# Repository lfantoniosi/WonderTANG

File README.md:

# WonderTANG

# NOTE: New firmware for 2.02b boards at:

https://github.com/lfantoniosi/new-juice

## TangNano 20K cartridge for MSX computers

This cartridge allows any MSX computer to host a Sipeed Tang Nano 20K. The current fpga core implements:

- MicroSD Nextor 2.1 Drive
- FM OPLL + MSX Music ROM
- 2MB Super Mega RAM SCC+
- 4MB Memory Mapper
- Sega Master System VDP + PSG to allow running SMS roms from SofaRun (Franky HDMI)

## The Super Mega RAM SCC+

The Super Mega RAM SCC+ is a different ACVS-like MegaRam that support different mappers:

- Konami4 (2MB)
- Konami5 SCC+ (512KB)
- ASCII8 (2MB)
- ASCII16 (2MB)

Use the utility SMRAM.COM to allow using different mappers as well activating the SCC+, otherwise it will just work like an ordinary MegaRAM 2MB.

## Board Revisions

The latest available version is [V2.0b](#v20av20b-new). Please, use that version to order new boards.

> [!IMPORTANT]
> Always check your board revision when assembling or programming your WonderTANG.
>
> The revision number is available on the front-left side of the board.
>
> Download the specific [FPGA Bitstream version](#fpga-bitstream-versions) required by your board version.

### [V2.0a/V2.0b (NEW)](https://github.com/lfantoniosi/WonderTANG/tree/4a21359a5136a5a96363da55edc5d934acfd37c5/kicad/)

This is the new version using Tang Nano 20K internal DAC amplifier.

Changes since last revision:
* uses internal DAC for audio output
* switches to a flatter audio connector
* removes jumpers
* requires the latest [FPGA bitstream version](#fpga-bitstream-versions)

V2.0a is equivalent to V2.0b.

||
|:--|
|V2.0a prototype build|

|||
|-|-|
|V2.0b front render|V2.0b back render|

#### PCB

You can access V2.0b gerber files from github at:

[https://github.com/lfantoniosi/WonderTANG/tree/4a21359a5136a5a96363da55edc5d934acfd37c5/kicad/gerber](https://github.com/lfantoniosi/WonderTANG/tree/4a21359a5136a5a96363da55edc5d934acfd37c5/kicad/gerber)

I recommend JLCPCB: https://jlcpcb.com/

#### Bill of Materials

| Reference                   | Value                      | Description                                          | Qty | Link        |
|-----------------------------|----------------------------|------------------------------------------------------|-----|-------------|
| C5, C6, C7, C8, C9, C10, C11, C12 | DIP-100NF                  | MLCC Monolithic Ceramic Capacitor DIP 100nF (104)     | 8   | AliExpress  |
| C1, C2                      | ELEC-DIP-4.7UF-16V         | Electrolytic Capacitor DIP 4.7uF 16V                 | 2   | AliExpress  |
| C13                         | ELEC-DIP-10UF-16V          | Electrolytic Capacitor DIP 10uF 16V                  | 1   | AliExpress  |
| R5,R6                       | DIP-2.2K                   | Resistor PTH 2.2KR                                   | 2   | Aliexpress  |
| R1                          | DIP-330R                   | Resistor PTH 330R                                    | 1   | AliExpress  |
| R4                          | DIP-4.7K                   | Resistor PTH 4.7KR                                   | 1   | AliExpress  |
| D1                          | LED-3MM                    | LED 3MM Red                                          | 1   | AliExpress  |
| D2                          | 1N5817                     | SCHOTTKY BARRIER RECTIFIER DIODE                    | 1   | AliExpress  |
| U1, U2, U3, U4, U6          | SOCKET-DIP-NARROW-20       | DIP Socket Narrow 20 pins                            | 5   | AliExpress  |
| U1, U2, U3, U4, U6          | SN74LVC245AN               | OCTAL BUS TRANSCEIVER WITH 3-STATE OUTPUTS           | 5   | See note    |
| Q1,Q2                       | 2N3904                     | 2N3904 NPN switching Transistor                      | 2   | AliExpress  |
| J2                          | CP1-3523N                  | CONN JACK STEREO 3.5MM R/A                           | 1   | AliExpress  |
| J3                          | Mini Micro male/female JST | Mini Micro male/female JST                           | 1   | AliExpress  |
| U5                          | Tang Nano 20K              | Tang Nano 20K                                        | 1   | AliExpress  |

#### Build Notes

The audio J3 needs to be soldered into the TANG Nano 20K speaker pins (two small pins between the words SiPEED and TANG NANO 20K, polarity does not matter). Use the JST connector or solder it directly under the board.

#### 74LVC245AN

Be aware of fake 74VLC245 sold from Chinese vendors like AliExpress or UTSource. There are reports of they being 74LS245 rebranded as LVC which does not work. You need genuine 75LVC245. Buy then from DigiKey, Mouser or Adafruit.

### [V1.02d (PREVIOUS)](https://github.com/lfantoniosi/WonderTANG/tree/0e938fb70acad34c753a95fd54bb3fdd6095d590/kicad/)

> [!WARNING]
> If you are building new boards, please use the latest available board revision instead.

This version fixes a problem with Philips MSX machines (detected on [Philips VG8235](https://www.msx.org/wiki/Philips_VG-8235) and [Philips NMS8245](https://www.msx.org/wiki/Philips_NMS_8245)) by properly implementing the MSX cartridge nINT signal as an open-collector.

Changes since last revision:
* uses a transistor to implement nINT as open-collector
* requires a specific [FPGA bitstream version](#fpga-bitstream-versions)

|||
|-|-|
|V1.02d front render|V1.02d back render|

#### PCB

You can access V1.02d gerber files from github at:

[https://github.com/lfantoniosi/WonderTANG/tree/0e938fb70acad34c753a95fd54bb3fdd6095d590/kicad/gerber](https://github.com/lfantoniosi/WonderTANG/tree/0e938fb70acad34c753a95fd54bb3fdd6095d590/kicad/gerber)

#### Bill of Materials

| Reference                   | Value                      | Description                                          | Qty | Link        |
|-----------------------------|----------------------------|------------------------------------------------------|-----|-------------|
| C5, C6, C7, C8, C9, C10, C11, C12 | DIP-100NF                  | MLCC Monolithic Ceramic Capacitor DIP 100nF (104)     | 8   | AliExpress  |
| C1, C3, C13                 | ELEC-DIP-10UF-16V          | Electrolytic Capacitor DIP 10uF 16V                  | 3   | AliExpress  |
| C2, C4                      | DIP-1UF                    | MLCC Monolithic Ceramic Capacitor DIP 1uF (105)      | 2   | AliExpress  |
| R2, R3                      | DIP-47R                    | Resistor PTH 47R                                     | 2   | AliExpress  |
| R5,R6                       | DIP-2.2K                   | Resistor PTH 2.2KR                                   | 2   | Aliexpress  |
| R1                          | DIP-330R                   | Resistor PTH 330R                                    | 1   | AliExpress  |
| R4                          | DIP-4.7K                   | Resistor PTH 4.7KR                                   | 1   | AliExpress  |
| D1                          | LED-3MM                    | LED 3MM Red                                          | 1   | AliExpress  |
| D2                          | 1N5817                     | SCHOTTKY BARRIER RECTIFIER DIODE                    | 1   | AliExpress  |
| U1, U2, U3, U4, U6          | SOCKET-DIP-NARROW-20       | DIP Socket Narrow 20 pins                            | 5   | AliExpress  |
| U1, U2, U3, U4, U6          | SN74LVC245AN               | OCTAL BUS TRANSCEIVER WITH 3-STATE OUTPUTS           | 5   | See note above  |
| Q1,Q2                       | 2N3904                     | 2N3904 NPN switching Transistor                      | 2   | AliExpress  |
| C13                         | ELEC-DIP-10UF-16V          | Electrolytic Capacitor DIP 10uF 16V                  | 1   | AliExpress  |
| C1, C2                      | ELEC-DIP-4.7UF-16V         | Electrolytic Capacitor DIP 7.7uF 16V                 | 2   | AliExpress  |
| J1, J3                      | PH-254-S-M-40-BLACK        | 2.54mm 1 x 40 Pin Male Single Row Pin Header Strip Black | 1 | AliExpress  |
| J2                          | SJ1-3533NG                 | SJ1-3533NG Audio P4 3 Pin connector                  | 1   | AliExpress  |
| U5                          | Tang Nano 20K              | Tang Nano 20K                                        | 1   | AliExpress  |

### [V1.01c (OBSOLETE)](https://github.com/lfantoniosi/WonderTANG/tree/b9e608418bb1917098046716af13b877def6737b/kicad/)

> [!WARNING]
> If you are building new boards, please use the latest available board revision instead.

This version corrects an audio problem due to wrong connection of AUDIO and SOUNDIN capacitors.

Changes since last revision:
* fix audio output
* requires an old [FPGA bitstream version](#fpga-bitstream-versions)

> [!IMPORTANT]
> This version is known to experience problems with some Philips MSX machines.

|||
|-|-|
|V1.01c front render|V1.01c back render|

#### PCB

You can access V1.01c gerber files from github at:

[https://github.com/lfantoniosi/WonderTANG/tree/b9e608418bb1917098046716af13b877def6737b/kicad/gerber](https://github.com/lfantoniosi/WonderTANG/tree/b9e608418bb1917098046716af13b877def6737b/kicad/gerber)

Or you can order V1.01c PCBs directly from:

[https://www.pcbway.com/project/shareproject/WonderTANG_v1_01c_ba2c16ea.html](https://www.pcbway.com/project/shareproject/WonderTANG_v1_01c_ba2c16ea.html)

A small part of the money will be donated to the author of the project.

#### Bill of Materials

| Reference                   | Value                      | Description                                          | Qty | Link        |
|-----------------------------|----------------------------|------------------------------------------------------|-----|-------------|
| C5, C6, C7, C8, C9, C10, C11, C12 | DIP-100NF                  | MLCC Monolithic Ceramic Capacitor DIP 100nF (104)     | 8   | AliExpress  |
| C1, C3, C13                 | ELEC-DIP-10UF-16V          | Electrolytic Capacitor DIP 10uF 16V                  | 3   | AliExpress  |
| C2, C4                      | DIP-1UF                    | MLCC Monolithic Ceramic Capacitor DIP 1uF (105)      | 2   | AliExpress  |
| R2, R3                      | DIP-47R                    | Resistor PTH 47R                                     | 2   | AliExpress  |
| R1                          | DIP-330R                   | Resistor PTH 330R                                    | 1   | AliExpress  |
| R4                          | DIP-4.7K                   | Resistor PTH 4.7KR                                   | 1   | AliExpress  |
| R5                          | DIP-2.2K                   | Resistor PTH 2.2KR                                   | 1   |             |
| D1                          | LED-3MM                    | LED 3MM Red                                          | 1   | AliExpress  |
| D2                          | 1N5817                     | SCHOTTKY BARRIER RECTIFIER DIODE                    | 1   | AliExpress  |
| U1, U2, U3, U4, U6          | SOCKET-DIP-NARROW-20       | DIP Socket Narrow 20 pins                            | 5   | AliExpress  |
| U1, U2, U3, U4, U6          | SN74LVC245AN               | OCTAL BUS TRANSCEIVER WITH 3-STATE OUTPUTS           | 5   | See note above  |
| Q1                          | 2N3904                     | 2N3904 NPN switching Transistor                      | 1   | AliExpress  |
| J1, J3                      | PH-254-S-M-40-BLACK        | 2.54mm 1 x 40 Pin Male Single Row Pin Header Strip Black | 1 | AliExpress  |
| J2                          | SJ1-3533NG                 | SJ1-3533NG Audio P4 3 Pin connector                  | 1   | AliExpress  |
| U5                          | Tang Nano 20K              | Tang Nano 20K                                        | 1   | AliExpress  |

### [V1.01b (OBSOLETE)](https://github.com/lfantoniosi/WonderTANG/tree/09ee5923f52284835864b947fba076c70dbe0fab/kicad/)

### [V1.01 (OBSOLETE)](https://github.com/lfantoniosi/WonderTANG/tree/d6cbb30488c2db2edb72d424ac75a0af0b1afaa3/kicad/)

### [V1.0 (OBSOLETE)](https://github.com/lfantoniosi/WonderTANG/tree/ac242e77184eeba1786766e48963c7b3fef0f877/kicad/)

## FPGA Bitstream Versions

If you want to program your WonderTANG you need to download the specific FPGA bitstream for your board revision according to the following table.

| Board Revision | FPGA Bitstream File                                                                                                                 |
| -------------- | ----------------------------------------------------------------------------------------------------------------------------------- |
| V1.0           | [WonderTANG_v1.0-v1.01c.fs](https://github.com/lfantoniosi/WonderTANG/blob/main/fpga/impl/pnr/WonderTANG_v1.0-v1.01c.fs?raw=True)             |
| V1.01          | [WonderTANG_v1.0-v1.01c.fs](https://github.com/lfantoniosi/WonderTANG/blob/main/fpga/impl/pnr/WonderTANG_v1.0-v1.01c.fs?raw=True)             |
| V1.01b         | [WonderTANG_v1.0-v1.01c.fs](https://github.com/lfantoniosi/WonderTANG/blob/main/fpga/impl/pnr/WonderTANG_v1.0-v1.01c.fs?raw=True)             |
| V1.01c         | [WonderTANG_v1.0-v1.01c.fs](https://github.com/lfantoniosi/WonderTANG/blob/main/fpga/impl/pnr/WonderTANG_v1.0-v1.01c.fs?raw=True)             |
| V1.02d         | [WonderTANG_v1.02d.fs](https://github.com/lfantoniosi/WonderTANG/blob/main/fpga/impl/pnr/WonderTANG_v1.02d.fs?raw=True)                  |
| V2.0b          | [WonderTANG.fs](https://github.com/lfantoniosi/WonderTANG/blob/main/fpga/impl/pnr/WonderTANG.fs?raw=True)                         |

## Programming the Cartridge

### How to Program the Tang Nano 20K from Windows

Install the Gowin Educative IDE or just the programmer if you want to just flash the files on your board. You can install it from https://www.gowinsemi.com/ by providing your personal data and registering. Please reboot your computer after installing the drivers.

Connect your TangNano board to the computer USB and open the Gowin Programmer software. Please note that we will be just programming the board, so you will not effectively use the IDE at this time. You should see the following message indicating that your board/cable was recognized. 

NOTE: for version 2.0b the FPGA core re-uses JTAG pins. So once flashed to re-flash the tang you need to press S1 button on it before connecting the USB-C cable and keep it pressed during all the time of the flashing process.

Click Add Device. You will see a new device on the list. Click on the Series and select GW2AR.

Now double click the device on the list and set Access Mode = External Flash Mode, Operation = exFlash Erase, Program thru GAO-Bridge. Click the elipsis and **select the __specific .fs file__ for your WonderTANG board revision** (see [FPGA bitstream versions](#fpga-bitstream-versions)). Select Generic Flash as the Device and make sure the address 0x000000 is selected. Click Save.

Click Add Device again. Set the Series to GW2AR. Double click on the device and set Access Mode = External Flash Mode, select Operation = exFlash C Bin Erase, Program thru GAO-Bridge. Click the elipsis and select the Nextor-2.1.1.WonderTANG.ROM.bin file. Select Generic Flash as the Device and make sure the address 0x100000 is selected. Click Save.

Now Enable just the first device on the list, go to the Edit menu and select Program/Configure (or click the program button).

<div style="display: flex; justify-content: space-between;">
     &nbsp;
    
</div>
&nbsp;

Repeat the steps now enabling just the second device on the list. That will save the BIOS on the flash.

<div style="display: flex; justify-content: space-between;">
     &nbsp;
    
</div>
&nbsp;

### How to Program the Tang Nano 20K from Linux

As the native programmer of the Gowin IDE does not properly work in Linux, it is recommended to use [openFPGALoader](https://github.com/trabucayre/openFPGALoader) to program the Tang Nano 20K of the WonderTANG.

This procedure has been tested successfully using openFPGALoader v0.10.0.

Assuming that you already downloaded **the __specific .fs file__ for your WonderTANG board revision** (see [FPGA bitstream versions](#fpga-bitstream-versions)) and `Nextor-2.1.1.WonderTANG.ROM` files, and that your Tang Nano 20K is connected to your computer using a USB cable, you can proceed as follows:

* Upload the bitstream (in this case `path_to_your/WonderTANG/fpga/impl/pnr/WonderTang.fs`) using the following command:

```
openFPGALoader -f -b tangnano20k --external-flash path_to_your/WonderTANG/fpga/impl/pnr/WonderTANG.fs
```

* Upload the WonderTANG ROM file `path_to_your/WonderTANG/kernel/Tang/Nextor-2.1.1.WonderTANG.ROM` using the following command:

```
openFPGALoader -f -b tangnano20k --external-flash -o 1048576 path_to_your/WonderTANG/kernel/Tang/Nextor-2.1.1.WonderTANG.ROM
```

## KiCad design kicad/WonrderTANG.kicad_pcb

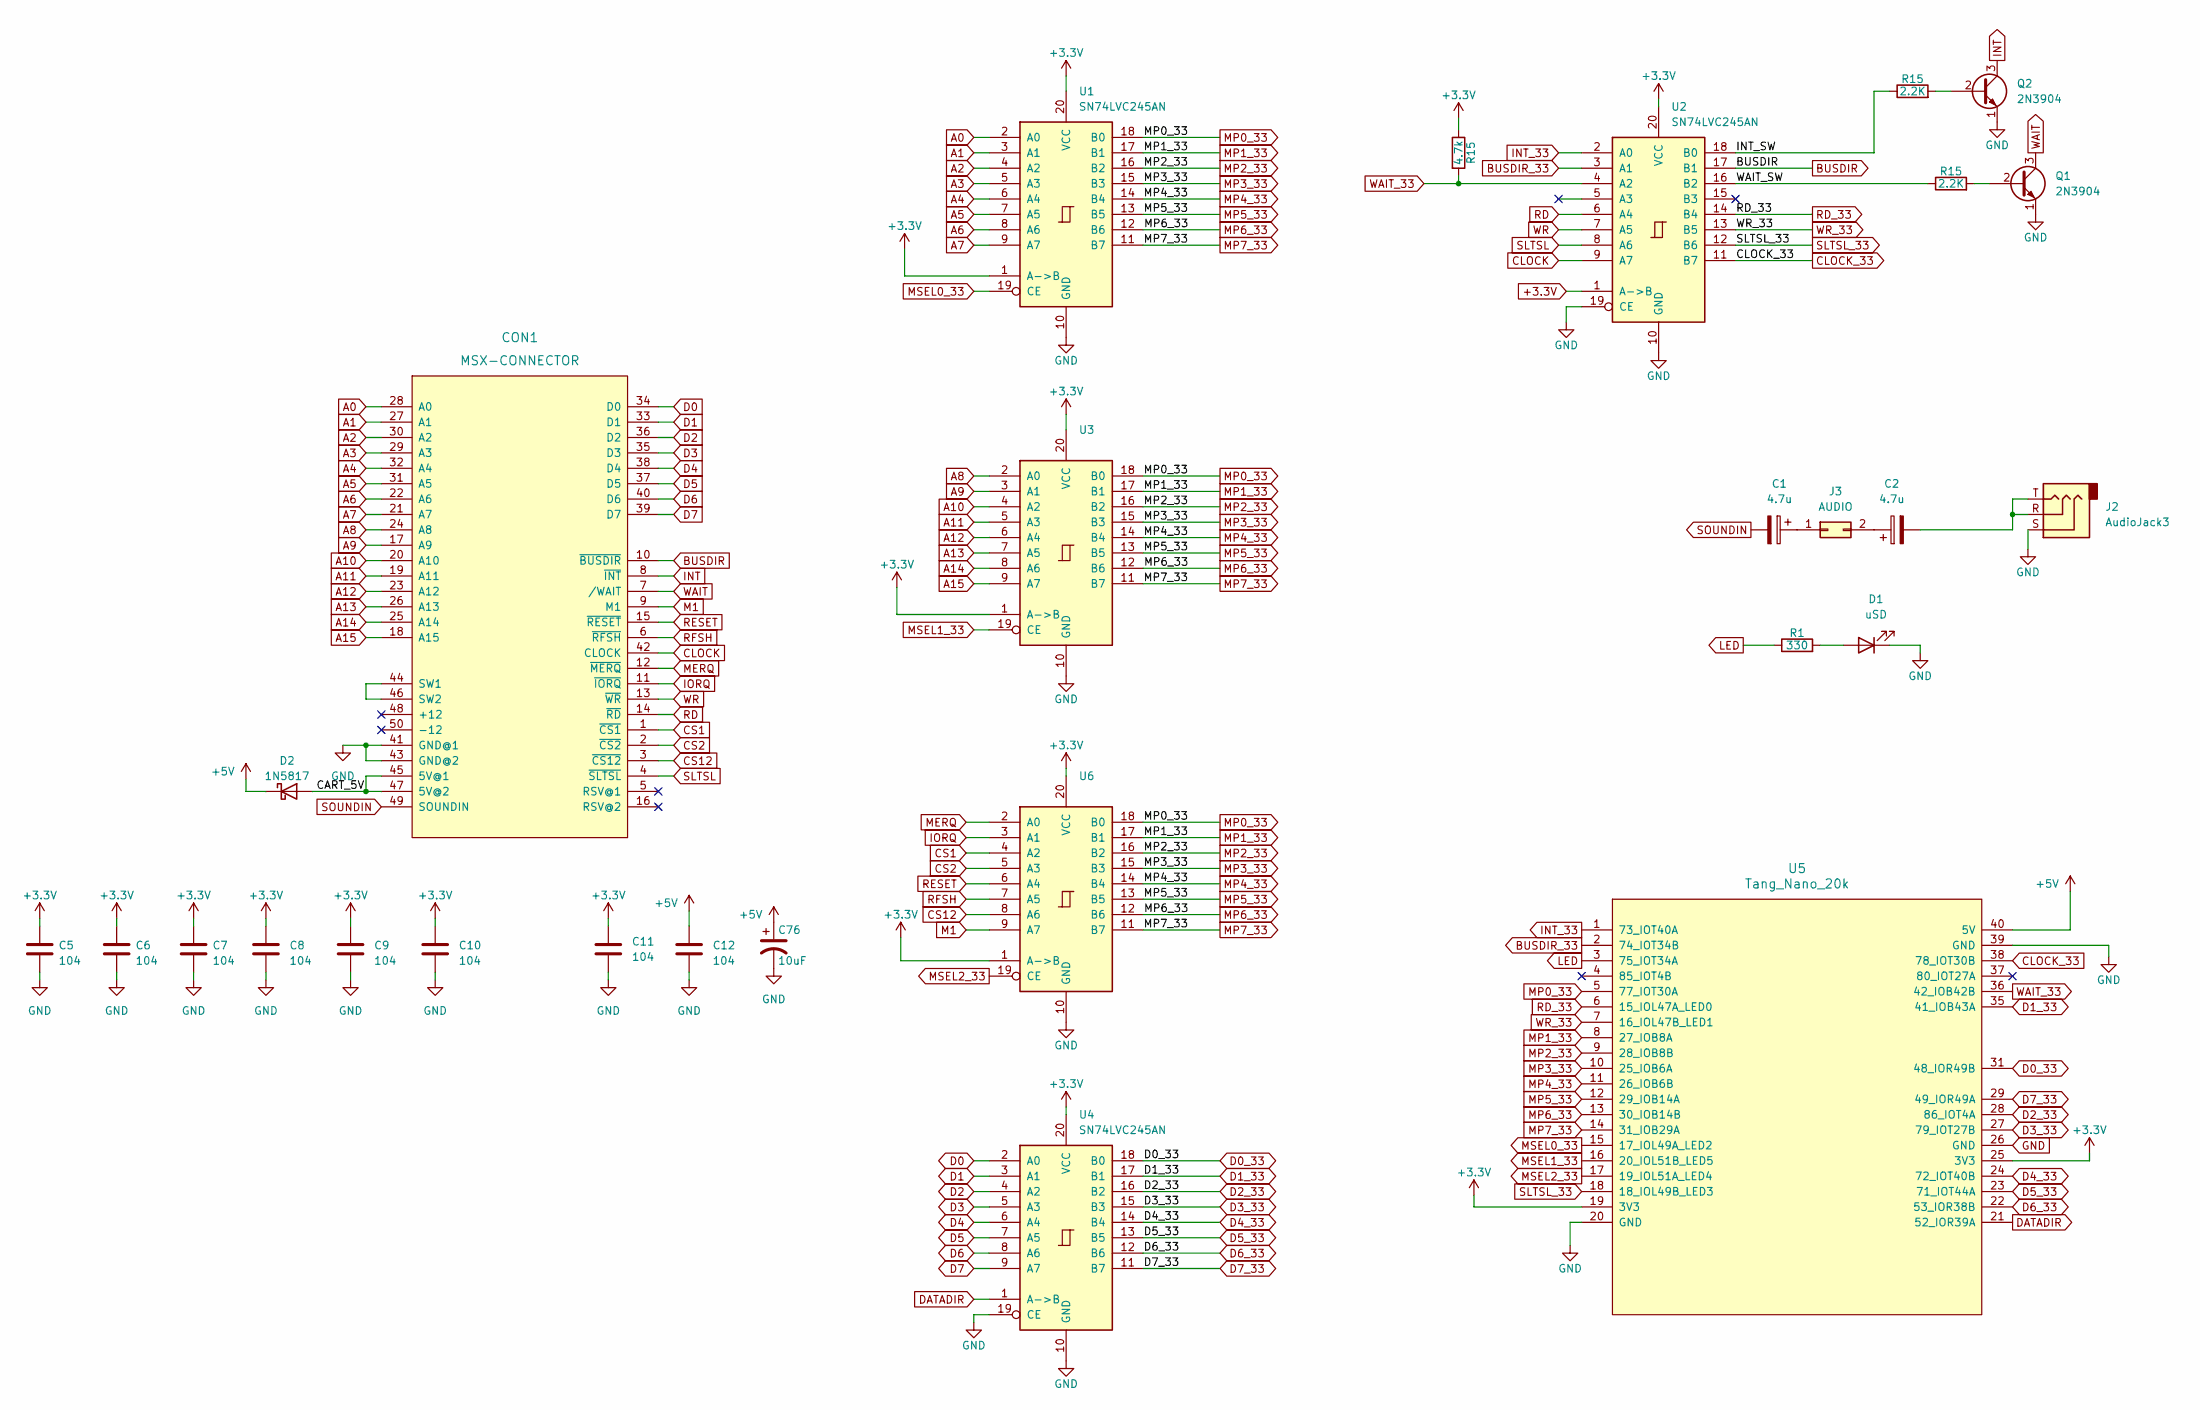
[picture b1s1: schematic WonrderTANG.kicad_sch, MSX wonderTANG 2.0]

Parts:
C1, C2: 4.7u; CP_Radial_D5.0mm_P2.50mm
C5, C6, C7, C8, C9, C10, C11, C12: 104; C_Disc_D5.0mm_W2.5mm_P2.50mm
C76: 10uF; CP_Radial_D5.0mm_P2.00mm
CON1: MSX-CONNECTOR; CARTRIDGE_MSX_NOCUT
D1: uSD; LED_D3.0mm
D2: 1N5817; D_DO-41_SOD81_P10.16mm_Horizontal
J2: AudioJack3; SJ1-3523N
J3: AUDIO; PinHeader_2x01_P2.54mm_Vertical
Q1, Q2: 2N3904; TO-92_Inline_Wide
R1: 330; R_Axial_DIN0207_L6.3mm_D2.5mm_P10.16mm_Horizontal
R15: 2.2K; R_Axial_DIN0207_L6.3mm_D2.5mm_P10.16mm_Horizontal
U1, U2, U3, U4, U6: SN74LVC245AN; DIP-20_W7.62mm_LongPads
U5: Tang_Nano_20k; Tang_Nano_20k_Audio

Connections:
+3.3V: C5.1, C6.1, C7.1, C8.1, C9.1, C10.1, C11.1, U1.1 (A->B), U1.20 (VCC), U2.1 (A->B), U2.20 (VCC), U3.1 (A->B), U3.20 (VCC), U4.20 (VCC), U5.19 (3V3), U5.25 (3V3), U6.1 (A->B), U6.20 (VCC); also elsewhere on the board
+5V: C12.1, D2.1 (K), U5.40 (5V); also elsewhere on the board
/CART_5V: CON1.45 (5V@1), CON1.47 (5V@2), D2.2 (A)
/INT_SW: U2.18 (B0); also elsewhere on the board
/WAIT_SW: U2.16 (B2); also elsewhere on the board
A0: CON1.28 (A0), U1.2 (A0)
A1: CON1.27 (A1), U1.3 (A1)
A2: CON1.30 (A2), U1.4 (A2)
A3: CON1.29 (A3), U1.5 (A3)
A4: CON1.32 (A4), U1.6 (A4)
A5: CON1.31 (A5), U1.7 (A5)
A6: CON1.22 (A6), U1.8 (A6)
A7: CON1.21 (A7), U1.9 (A7)
A8: CON1.24 (A8), U3.2 (A0)
A9: CON1.17 (A9), U3.3 (A1)
A10: CON1.20 (A10), U3.4 (A2)
A11: CON1.19 (A11), U3.5 (A3)
A12: CON1.23 (A12), U3.6 (A4)
A13: CON1.26 (A13), U3.7 (A5)
A14: CON1.25 (A14), U3.8 (A6)
A15: CON1.18 (A15), U3.9 (A7)
BUSDIR: CON1.10 (~BUSDIR), U2.17 (B1)
BUSDIR_33: U2.3 (A1), U5.2 (74_IOT34B)
CLOCK: CON1.42 (CLOCK), U2.9 (A7)
CLOCK_33: U2.11 (B7), U5.38 (78_IOT30B)
CS1: CON1.1 (~CS1), U6.4 (A2)
CS2: CON1.2 (~CS2), U6.5 (A3)
CS12: CON1.3 (~CS12), U6.8 (A6)
D0: CON1.34 (D0), U4.2 (A0)
D0_33: U4.18 (B0), U5.31 (48_IOR49B)
D1: CON1.33 (D1), U4.3 (A1)
D1_33: U4.17 (B1), U5.35 (41_IOB43A)
D2: CON1.36 (D2), U4.4 (A2)
D2_33: U4.16 (B2), U5.28 (86_IOT4A)
D3: CON1.35 (D3), U4.5 (A3)
D3_33: U4.15 (B3), U5.27 (79_IOT27B)
D4: CON1.38 (D4), U4.6 (A4)
D4_33: U4.14 (B4), U5.24 (72_IOT40B)
D5: CON1.37 (D5), U4.7 (A5)
D5_33: U4.13 (B5), U5.23 (71_IOT44A)
D6: CON1.40 (D6), U4.8 (A6)
D6_33: U4.12 (B6), U5.22 (53_IOR38B)
D7: CON1.39 (D7), U4.9 (A7)
D7_33: U4.11 (B7), U5.29 (49_IOR49A)
DATADIR: U4.1 (A->B), U5.21 (52_IOR39A)
GND: C5.2, C6.2, C7.2, C8.2, C9.2, C10.2, C11.2, C12.2, CON1.41 (GND@1), CON1.43 (GND@2), D1.1 (K), J2.S, Q1.1 (E), Q2.1 (E), U1.10 (GND), U2.10 (GND), U2.19 (CE), U3.10 (GND), U4.10 (GND), U4.19 (CE), U5.20 (GND), U5.26 (GND), U5.39 (GND), U6.10 (GND); also elsewhere on the board
INT: CON1.8 (~INT), Q2.3 (C)
INT_33: U2.2 (A0), U5.1 (73_IOT40A)
IORQ: CON1.11 (~IORQ), U6.3 (A1)
LED: R1.1, U5.3 (75_IOT34A)
M1: CON1.9 (M1), U6.9 (A7)
MERQ: CON1.12 (~MERQ), U6.2 (A0)
MP0_33: U1.18 (B0), U3.18 (B0), U5.5 (77_IOT30A), U6.18 (B0)
MP1_33: U1.17 (B1), U3.17 (B1), U5.8 (27_IOB8A), U6.17 (B1)
MP2_33: U1.16 (B2), U3.16 (B2), U5.9 (28_IOB8B), U6.16 (B2)
MP3_33: U1.15 (B3), U3.15 (B3), U5.10 (25_IOB6A), U6.15 (B3)
MP4_33: U1.14 (B4), U3.14 (B4), U5.11 (26_IOB6B), U6.14 (B4)
MP5_33: U1.13 (B5), U3.13 (B5), U5.12 (29_IOB14A), U6.13 (B5)
MP6_33: U1.12 (B6), U3.12 (B6), U5.13 (30_IOB14B), U6.12 (B6)
MP7_33: U1.11 (B7), U3.11 (B7), U5.14 (31_IOB29A), U6.11 (B7)
MSEL0_33: U1.19 (CE), U5.15 (17_IOL49A_LED2)
MSEL1_33: U3.19 (CE), U5.16 (20_IOL51B_LED5)
MSEL2_33: U5.17 (19_IOL51A_LED4), U6.19 (CE)
unnamed: C2.2, J2.R, J2.T
unnamed: CON1.44 (SW1), CON1.46 (SW2)
unnamed: D1.2 (A), R1.2
unnamed: C1.1, J3.1
unnamed: C2.1, J3.2
unnamed 68: Q1.2 (B); also elsewhere on the board
unnamed 69: Q2.2 (B); also elsewhere on the board
RD: CON1.14 (~RD), U2.6 (A4)
RD_33: U2.14 (B4), U5.6 (15_IOL47A_LED0)
RESET: CON1.15 (~RESET), U6.6 (A4)
RFSH: CON1.6 (~RFSH), U6.7 (A5)
SLTSL: CON1.4 (~SLTSL), U2.8 (A6)
SLTSL_33: U2.12 (B6), U5.18 (18_IOL49B_LED3)
SOUNDIN: C1.2, CON1.49 (SOUNDIN)
WAIT: CON1.7 (/WAIT), Q1.3 (C)
WAIT_33: U2.4 (A2), U5.36 (42_IOB42B); also elsewhere on the board
WR: CON1.13 (~WR), U2.7 (A5)
WR_33: U2.13 (B5), U5.7 (16_IOL47B_LED1)

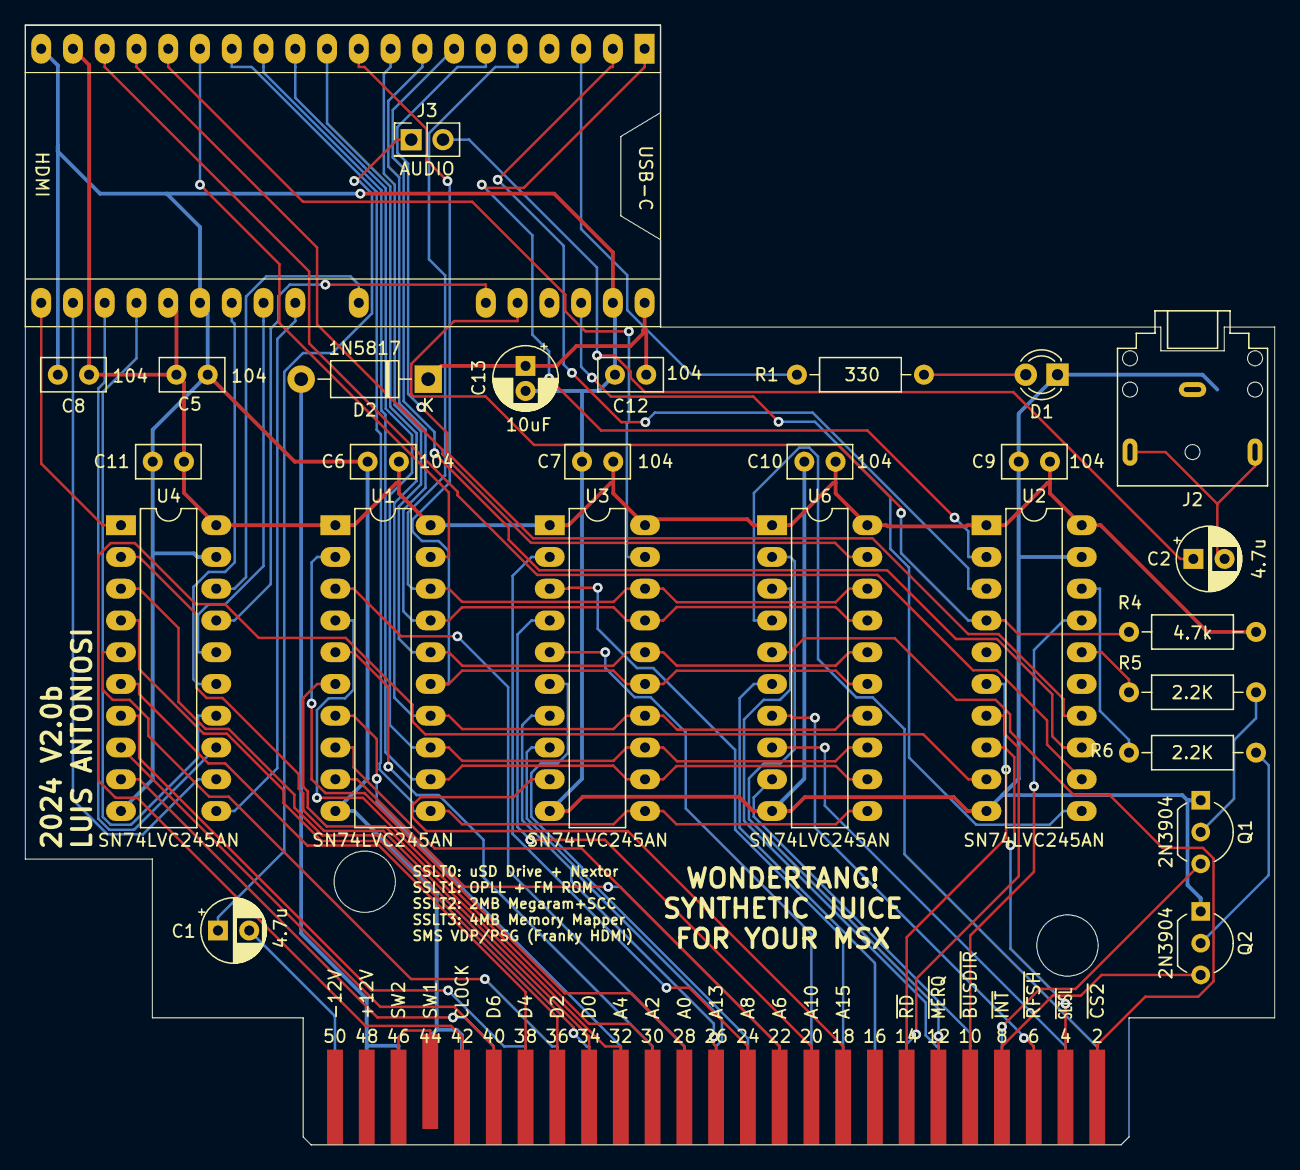
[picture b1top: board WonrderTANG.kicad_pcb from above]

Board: 2 copper layers, 99.9 x 89.5 mm, 28 parts (0 on the bottom side), 81 nets.

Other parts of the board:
C13: 10uF; CP_Radial_D5.0mm_P2.00mm
R4: 4.7k; R_Axial_DIN0207_L6.3mm_D2.5mm_P10.16mm_Horizontal
R5, R6: 2.2K; R_Axial_DIN0207_L6.3mm_D2.5mm_P10.16mm_Horizontal

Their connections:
+3.3V: R4.1; also elsewhere on the board
+5V: C13.1; also elsewhere on the board
/INT_SW: R6.1; also elsewhere on the board
/WAIT_SW: R5.1; also elsewhere on the board
GND: C13.2; also elsewhere on the board
unnamed 68: R5.2; also elsewhere on the board
unnamed 69: R6.2; also elsewhere on the board
WAIT_33: R4.2; also elsewhere on the board

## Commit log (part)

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2023-09-26 fpga code
2023-09-27 smram tool
2023-09-30 kicad
2023-10-09 adding activity LED
2023-10-11 make SMS configurable, pulldown on WAIT line
2023-10-16 fix on wait line
2023-10-16 fix clock speed turboR
2023-10-18 driver update
2023-10-18 adding sms PSG
2023-10-18 disable SMS VDP on boot
2023-10-19 unused vars
2023-10-19 kicad final version 1.01
2023-10-19 delete
2023-10-19 update comments
2023-10-28 kicad fixes
    fix shorted transistor add 10uf power line, moved cap to allow be placed horizontally
2023-11-05 Allow support to HC-95 in turbo mode (use HC-95 rom)
2023-11-05 merged version
2023-11-11 fix pinfilter (opll)
2023-11-12 adjustments
2023-11-12 fix SCC, needs to compile disabling pinfilter FASTREAD
    fastread is required for hc-95 in turbo mode
2023-11-13 SCC requires a slow merq
    fast merq (hc-95 turbo) was breaking SCC
2023-11-15 [kicad] Fix text thickness out of range errors for U5
    Fixes text thickness out of range errors for "HDMI"
    and "USB-C" texts of U5 by increasing text thickness
    from 0.1 to 0.15.
2023-11-15 [kicad] Fix board edge clearance violation errors
    PCB edge connectors pad types are currently declared as SMD instead of
    Edge Connector which causes 49 board edge clearance violation errors
    when running the DRC (Design Rules Checker).
    Fix those by declaring the edge connectors pad types as Edge Connector.
2023-11-15 [kicad] Fix silkscreen clipped by solder mask for cartridge pads
    Text for pads 3 "CS12" and 4 "SLTSL" fall within one of the holes
    used to fix the cartridge board to the cartridge case.
    Make those texts visible again by reducing text width so that they
    do not extend into the cartridge board hole.
2023-11-15 [kicad] Fix silkscreen overlap between Q1 and R5
2023-11-23 Fix board audio
    audio pins were connected together
2023-11-28 stl case, new rom
2023-12-31 Update README with programming instructions, BOM and lock removal
2024-01-01 Update README.md
    add PCB Way link
2024-02-06 fixing audio to cart (Audio jumper) was set to wrong pin
2024-05-04 [kicad] Fix CARTRIDGE_MSX footprint board edge clearance violation errors
    PCB edge connectors pad types are currently declared as SMD instead of
    Edge Connector which causes 49 board edge clearance violation errors
    when running the DRC (Design Rules Checker).
    Fix those by declaring the edge connectors pad types as Edge Connector.
2024-05-04 [kicad] show value for U4
    All SN74LVC245AN footprints show its value except U4.
    Fix that by adding its value to the silkscreen layer.
2024-05-04 [kicad] Silkscreen updates for cartridge pads
    Mark active low signals BDIR,CS1,CS2,CS12,INT,IRQ,M1,MRQ,RD,RFSH,RST,SLTSL,WAIT,WR with a bar above them.
    Add voltage suffix V to +5, +12 and -12 signals.
    Add pad number to pad 43.
    Add pad number to pad 44.
    Name each SW pad with its own names SW1 and SW2.
    Rename BDIR to BUSDIR.
2024-05-04 [kicad] Fix /CART_5V net width
    Update the PCB to bring /CART_5V in sync with the schematic.
    Apply the power netclass width to /CART_5V as it is currently using a
    smaller width than the rest of power nets (from the cartridge pads to the
    D2 diode).
    Add clearance when needed to account for the increase in net width.
2024-05-10 fix pathnames
2024-05-10 support to Gowin Beta 1.9.9 Beta-4
2024-05-10 fix audio source clk
2024-05-11 soound improments
    removing filters
    removing psg from cartridge sound port
2024-05-11 swap audio outputs for version 1.0c
2024-05-12 restrore scc on edge
2024-05-12 lower scc volume
2024-05-12 adding filters back
2024-05-16 Solving OMEGA MSX instability
2024-05-18 improving omega stability
2024-05-22 fpga: improve signal mux
    The WonderTANG uses a multiplexing scheme to read 24 signals using just
    8 pins through three 74LVC245 ICs.
    The multiplexing scheme is driven by a ~108MHz clock (~9.25ns period)
    using the following schedule based on a 8 cycle plan:
    - the first cycle is used to select A0-A7 signals and enable signal
    propagation (which is Ten=~4.4ns for the 74LVC245)
2024-05-22 omega stability
2024-05-23 make scc + 51KB megaram default
2024-05-24 change the initial megaram type. use nte smram.com
2024-05-24 fix scc merg line
2024-05-25 version d schematic
2024-05-25 ignore lock
2024-05-25 Revert "version d schematic"
    This reverts commit 586f92a0309d7defb717df5fd5272d4bcb2072a4.
2024-05-26 fix opll and some audio changes
2024-05-26 New PCB Version 1.0.2d
    A new firmware inverting the INT outpult needs to be submitted.
2024-06-19 version 2.0b
2024-06-19 new photos added
2024-06-19 fix hdmi audio / sms
2024-06-19 fix led
2024-06-19 disabling the volume control (it breaks SSMS)
2024-06-20 removing volume control not working
2024-06-20 document board revisions and bitstreams
2024-06-22 use jtopl instead
2024-06-22 kicad: sync schematic labels with pcb
2024-06-22 kicad: fix front solder mask aperture bridges items with different nets errors
2024-06-22 kicad: change audio connector from CP1-3523N to SJ1-3525N
2024-07-04 some changes
2024-07-05 shutdown rgb led reduce noise
2024-07-05 reset rgb led on msx reset button
2024-07-06 better timming on audio
2024-07-06 Changed pcb width to 99.965mm, reducing the pcbway fabrication cost fro 5 to , which is the standard cost to 5 protoboards. Only right side of the pcb was shifted left, no other changes were made
2024-07-06 Adjusted cut in the audio connector
2024-07-06 applied solder mask to edge connector
2024-07-06 gerber20b.zip removed due to changes in the pcb. if this pull request is commited, a new gerber should be generated by the author of the project and pushed to main repo.
2024-07-08 new v2.0 STL case
2024-07-09 make cartridge 1mm thinner
2024-07-11 Update README.md
    add 74LVC245 warning
2024-07-12 sms audio clipping in castle of illusion
2024-07-24 New audio mixing and volume control
    This patch simplifies the audio mixer and
    re-adds the volume control logic.
    Volume for the WonderTANG PSG, SCC+ and OPLL
    can be independently controlled using a software
    knob with 7 levels (0=no audio, 1-7=low to high).
    The SMRAM.COM tool can be used to set the different
2024-12-14 support to 7Mhz Turbo (including HC-95 Turbo)[A
2024-12-14 fix SCC again
2024-12-14 remove clock groups not helping
2024-12-14 incread clock frq on clock pin
2025-02-07 experimental-broken
2025-04-27 Improvements: 2MB SCC Megaram support over SMRAM.COM
2025-04-27 Revert "Improvements: 2MB SCC Megaram support over SMRAM.COM"
    This reverts commit 0f1f167a547db2edea37f5e8a9484623ee36b683.
2025-04-28 set 2MB megaram SCC as default. Unfortunately Super Mario World has a game protection agains megaflashroms so it won't work if not patched. I would need to create a new strict SCC ROM mode which woul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
2025-04-29 Support for SuperMario World and Street Fighter. Use the new SRAM.COM with the /K5 option. The default options is megaram SCC but these games require strict SCC addressing. Using K5 comply with them.
2025-04-29 fix some meta-stability - SOFARUN still has SCC broken
